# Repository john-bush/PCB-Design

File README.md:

# PCB-Design
PCB Design Projects for RoboLAND Lab

Subfolders contain Eagle project files for a Differential AS5048A Positional encoder and a Differential Master board to interface with an ODrive motor controller board.

The boards utilize IX Industrial connector cables.

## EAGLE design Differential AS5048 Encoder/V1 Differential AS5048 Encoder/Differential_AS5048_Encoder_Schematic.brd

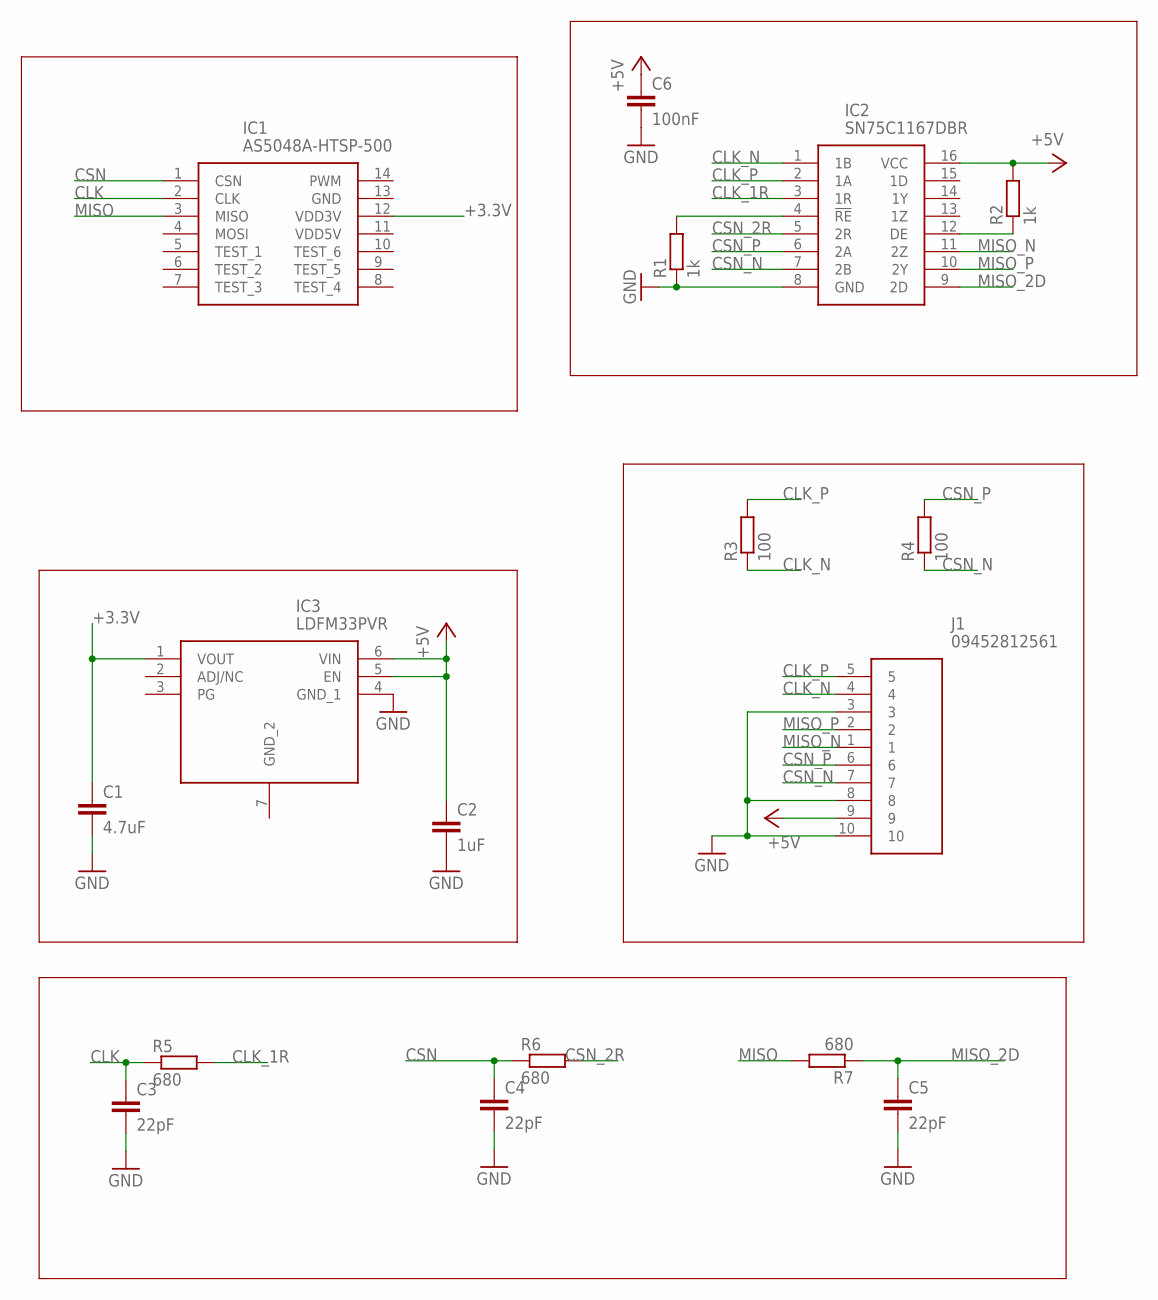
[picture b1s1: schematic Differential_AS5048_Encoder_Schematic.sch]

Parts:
C1: 4.7uF; C0603
C2: 1uF; C0603
C3, C4, C5: 22pF; C0603
C6: 100nF; C0603
IC1: AS5048A-HTSP-500; SOP65P640X120-14N
IC2: SN75C1167DBR; SOP65P780X200-16N
IC3: LDFM33PVR; SON65P200X200X100-7N
J1: 09452812561
R1, R2: 1k; R0603
R3, R4: 100; R0603
R5, R6, R7: 680; R0603

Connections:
+3.3V: C1.1, IC1.12 (VDD3V), IC3.1 (VOUT)
+5V: C2.1, C6.1, IC2.16 (VCC), IC3.5 (EN), IC3.6 (VIN), J1.9, R2.2
CLK: C3.1, IC1.2 (CLK), R5.1
CLK_1R: IC2.3 (1R), R5.2
CLK_N: IC2.1 (1B), J1.4, R3.1
CLK_P: IC2.2 (1A), J1.5, R3.2
CSN: C4.1, IC1.1 (CSN), R6.1
CSN_2R: IC2.5 (2R), R6.2
CSN_N: IC2.7 (2B), J1.7, R4.1
CSN_P: IC2.6 (2A), J1.6, R4.2
GND: C1.2, C2.2, C3.2, C4.2, C5.2, C6.2, IC2.8 (GND), IC3.4 (GND_1), J1.3, J1.8, J1.10, R1.1
MISO: IC1.3 (MISO), R7.2
MISO_2D: C5.1, IC2.9 (2D), R7.1
MISO_N: IC2.11 (2Z), J1.1
MISO_P: IC2.10 (2Y), J1.2
unnamed: IC2.4 (!RE), R1.2
unnamed: IC2.12 (DE), R2.1

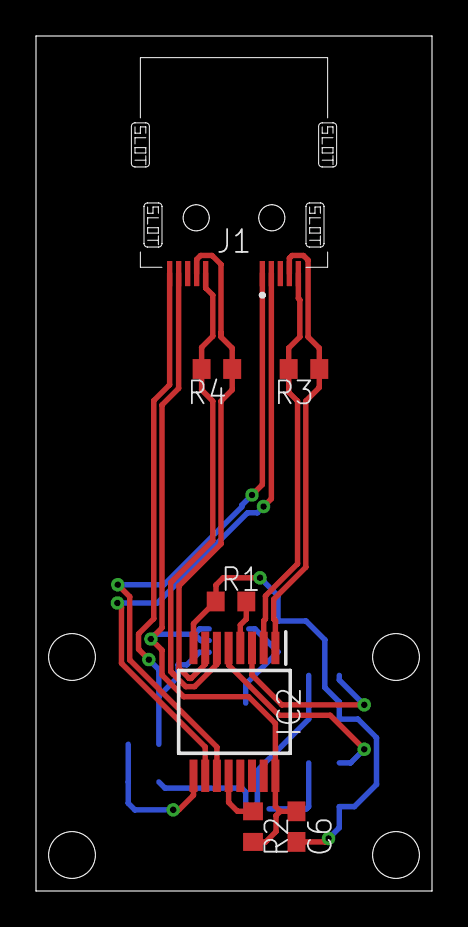
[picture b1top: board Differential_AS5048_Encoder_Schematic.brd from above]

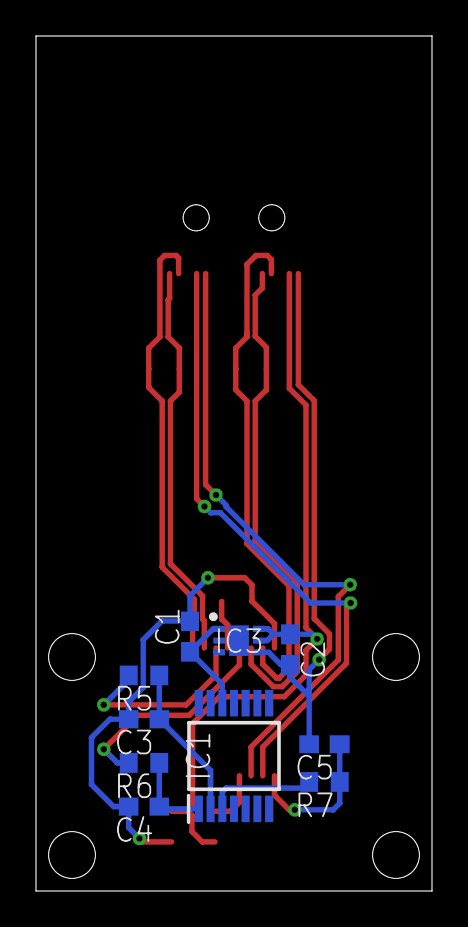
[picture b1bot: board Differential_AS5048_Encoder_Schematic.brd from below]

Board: 2 copper layers, 22.0 x 47.5 mm, 17 parts (10 on the bottom side), 17 nets.

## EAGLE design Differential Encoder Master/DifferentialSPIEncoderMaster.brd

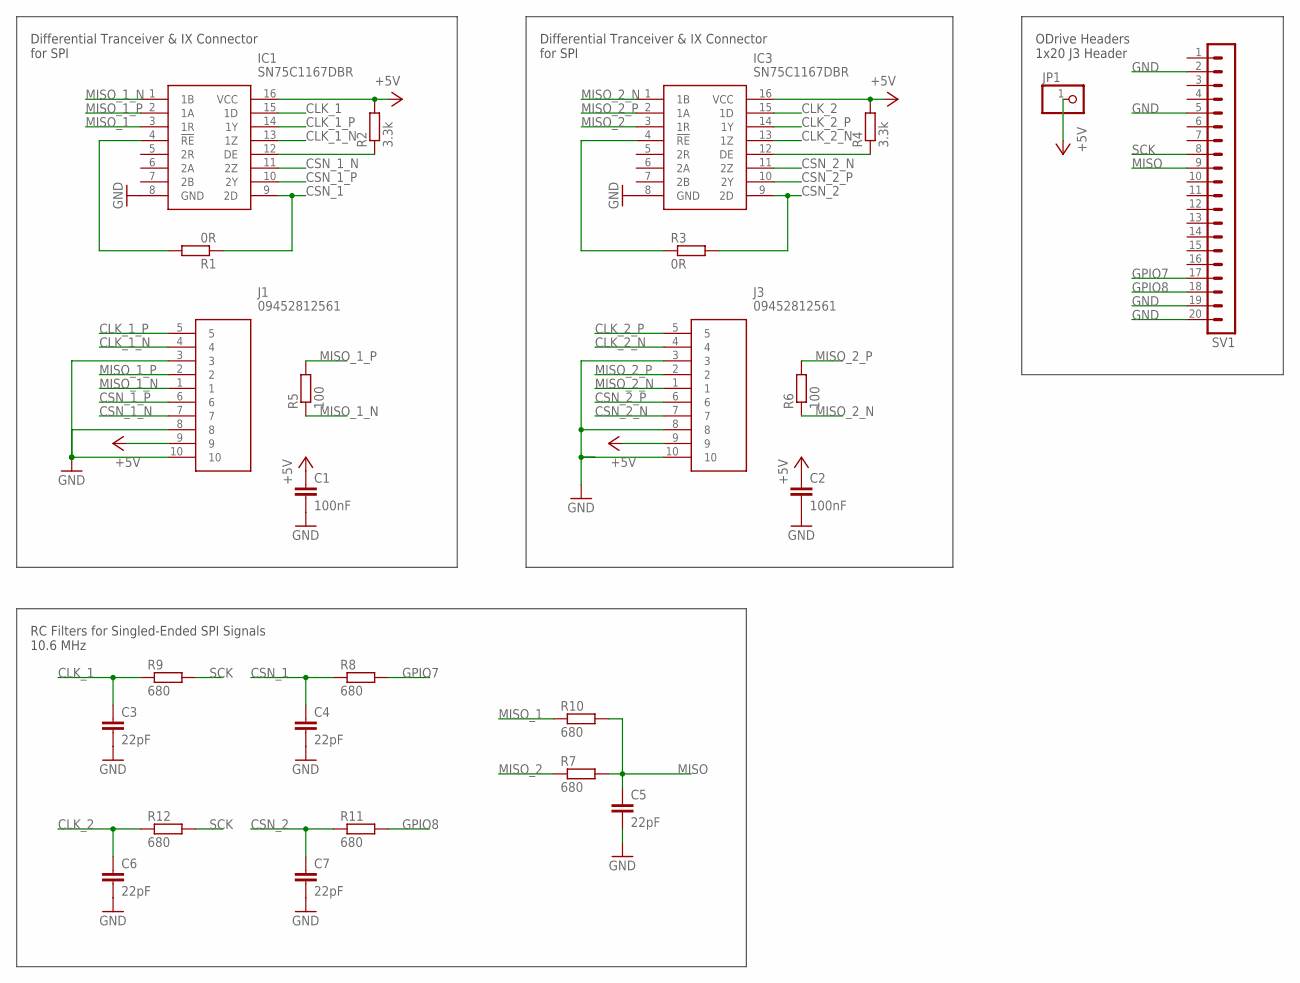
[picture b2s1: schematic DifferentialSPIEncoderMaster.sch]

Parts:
C1, C2: 100nF; C0603
C3, C4, C5, C6, C7: 22pF; C0603
IC1, IC3: SN75C1167DBR; SOP65P780X200-16N
J1, J3: 09452812561
JP1: PINHD-1X1; 1X01
R1, R3: 0R; R0603
R2, R4: 3.3k; R0603
R5, R6: 100; R0603
R7, R8, R9, R10, R11, R12: 680; R0603
SV1: MA20-1

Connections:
+5V: C1.1, C2.1, IC1.16 (VCC), IC3.16 (VCC), J1.9, J3.9, JP1.1, R2.2, R4.2
CLK_1: C3.1, IC1.15 (1D), R9.1
CLK_1_N: IC1.13 (1Z), J1.4
CLK_1_P: IC1.14 (1Y), J1.5
CLK_2: C6.1, IC3.15 (1D), R12.1
CLK_2_N: IC3.13 (1Z), J3.4
CLK_2_P: IC3.14 (1Y), J3.5
CSN_1: C4.1, IC1.4 (!RE), IC1.9 (2D), R1.1, R1.2, R8.1
CSN_1_N: IC1.11 (2Z), J1.7
CSN_1_P: IC1.10 (2Y), J1.6
CSN_2: C7.1, IC3.4 (!RE), IC3.9 (2D), R3.1, R3.2, R11.1
CSN_2_N: IC3.11 (2Z), J3.7
CSN_2_P: IC3.10 (2Y), J3.6
GND: C1.2, C2.2, C3.2, C4.2, C5.2, C6.2, C7.2, IC1.8 (GND), IC3.8 (GND), J1.3, J1.8, J1.10, J3.3, J3.8, J3.10, SV1.2, SV1.5, SV1.19, SV1.20
GPIO7: R8.2, SV1.17
GPIO8: R11.2, SV1.18
MISO: C5.1, R7.2, R10.2, SV1.9
MISO_1: IC1.3 (1R), R10.1
MISO_1_N: IC1.1 (1B), J1.1, R5.1
MISO_1_P: IC1.2 (1A), J1.2, R5.2
MISO_2: IC3.3 (1R), R7.1
MISO_2_N: IC3.1 (1B), J3.1, R6.1
MISO_2_P: IC3.2 (1A), J3.2, R6.2
unnamed: IC1.12 (DE), R2.1
unnamed: IC3.12 (DE), R4.1
SCK: R9.2, R12.2, SV1.8

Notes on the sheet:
RC Filters for Singled-Ended SPI Signals 10.6 MHz
ODrive Headers 1x20 J3 Header
Differential Tranceiver & IX Connector for SPI

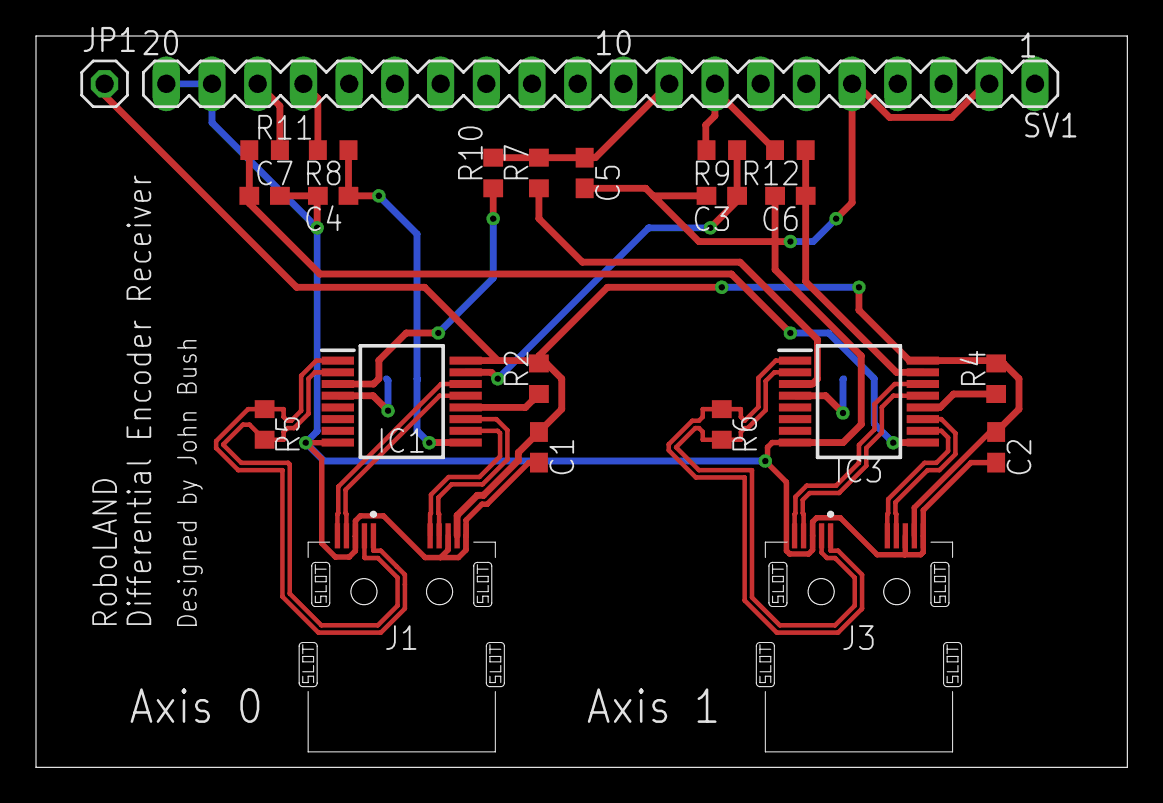
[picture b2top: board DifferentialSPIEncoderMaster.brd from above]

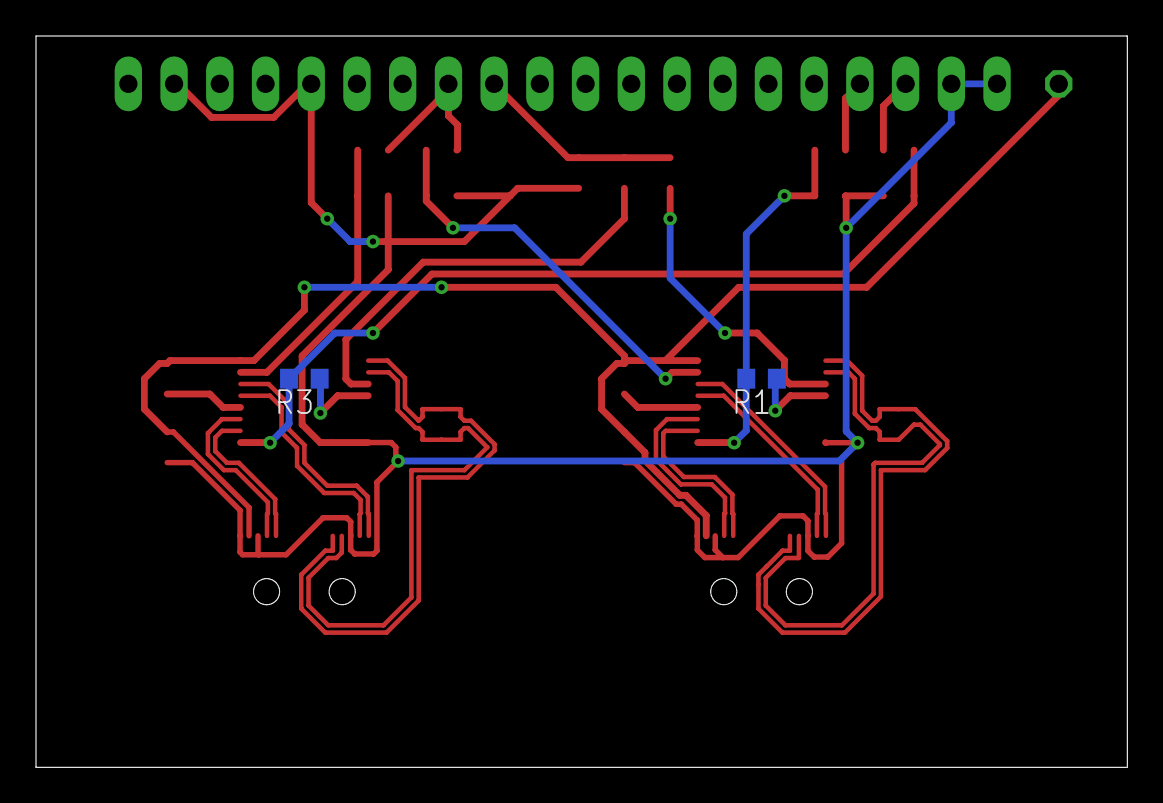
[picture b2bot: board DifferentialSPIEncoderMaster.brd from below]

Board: 2 copper layers, 60.6 x 40.6 mm, 25 parts (2 on the bottom side), 26 nets.

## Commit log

2021-07-13 Added project files
2021-07-13 Added board schematics
2021-08-01 Added V2 Encoder and Master boards
    V2-- redesigned PCBs in Altium as 4-layer boards with internal GND and Power Planes. Swapped components to standardized 0603 package components.
